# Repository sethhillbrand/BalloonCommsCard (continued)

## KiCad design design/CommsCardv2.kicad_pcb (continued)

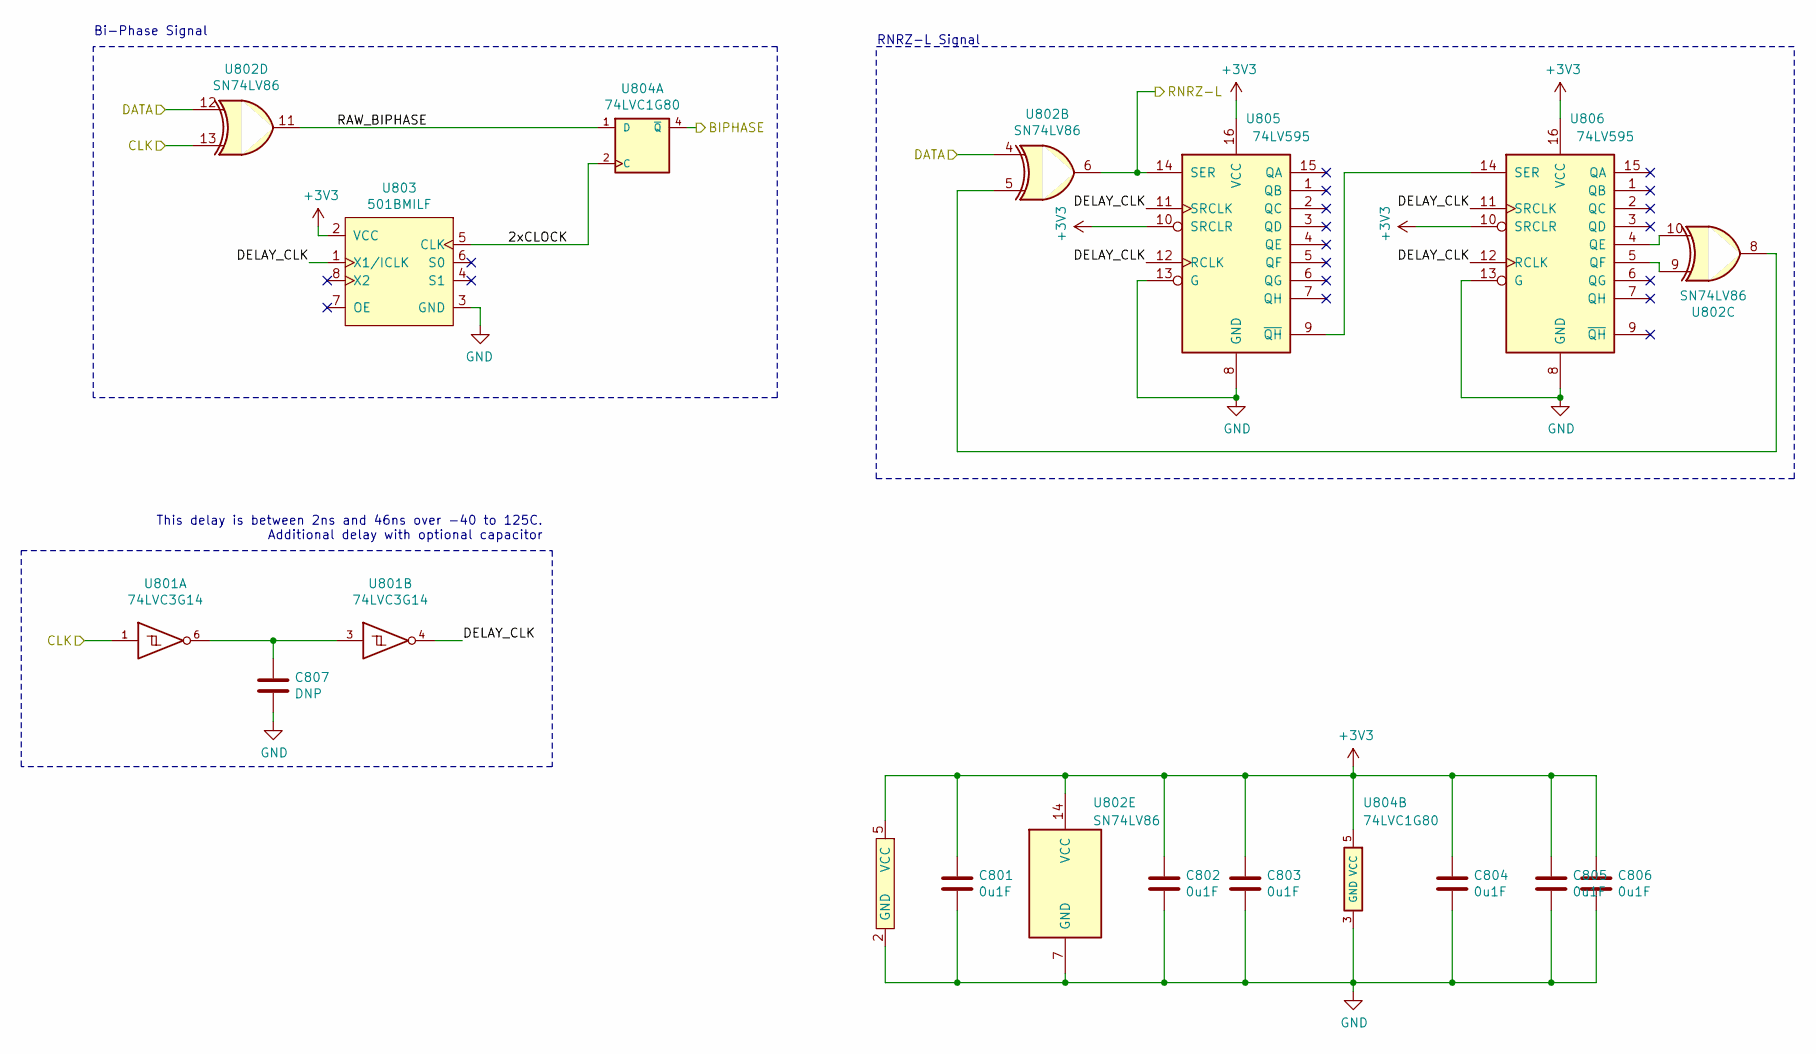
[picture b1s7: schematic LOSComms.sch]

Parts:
C601, C602, C603, C604, C605, C606: 0u1F; C_0603_1608Metric; mpn CL10B104KO8WPNC
C607: DNP; C_0603_1608Metric
U601: 74LVC3G14; SOT-363_SC-70-6; mpn 74LVC14AT14-13
U602: SN74LV86; TSSOP-14_4.4x5mm_P0.65mm; mpn SN74LV86ATPWREP
U603: 501BMILF; SOIC-8_3.9x4.9mm_P1.27mm; mpn 501BMILF
U604: 74LVC1G80; SOT-353_SC-70-5; mpn SN74LVC1G79DCKR
U605, U606: 74LV595; TSSOP-16_4.4x5mm_P0.65mm; mpn SN74LV595APWR

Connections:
/FlightComputer1/LOSComms/2xCLOCK: U603.5 (CLK), U604.2 (C)
/FlightComputer1/LOSComms/BIPHASE: U604.4 (~Q); also elsewhere on the board
/FlightComputer1/LOSComms/CLK: U601.1, U602.2, U602.13; also elsewhere on the board
/FlightComputer1/LOSComms/DATA: U602.1, U602.4, U602.12; also elsewhere on the board
/FlightComputer1/LOSComms/DELAY_CLK: U601.4, U603.1 (X1/ICLK), U605.11 (SRCLK), U605.12 (RCLK), U606.11 (SRCLK), U606.12 (RCLK)
/FlightComputer1/LOSComms/RAW_BIPHASE: U602.3, U602.11, U604.1 (D)
/FlightComputer1/LOSComms/RNRZ-L: U602.6, U605.14 (SER); also elsewhere on the board
GND: C601.2, C602.2, C603.2, C604.2, C605.2, C606.2, C607.2, U601.2 (GND), U602.7 (GND), U603.3 (GND), U604.3 (GND), U605.8 (GND), U605.13 (G), U606.8 (GND), U606.13 (G); also elsewhere on the board
unnamed: C607.1, U601.3, U601.6
unnamed: U602.5, U602.8
unnamed: U602.9, U606.5 (QF)
unnamed: U602.10, U606.4 (QE)
unnamed: U605.9 (~QH), U606.14 (SER)

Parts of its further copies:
C801, C802, C803, C804, C805, C806: 0u1F; C_0603_1608Metric; mpn CL10B104KO8WPNC
C807: DNP; C_0603_1608Metric
U801: 74LVC3G14; SOT-363_SC-70-6; mpn 74LVC14AT14-13
U802: SN74LV86; TSSOP-14_4.4x5mm_P0.65mm; mpn SN74LV86ATPWREP
U803: 501BMILF; SOIC-8_3.9x4.9mm_P1.27mm; mpn 501BMILF
U804: 74LVC1G80; SOT-353_SC-70-5; mpn SN74LVC1G79DCKR
U805, U806: 74LV595; TSSOP-16_4.4x5mm_P0.65mm; mpn SN74LV595APWR

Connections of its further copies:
/FlightComputer2/LOSComms/2xCLOCK: U803.5 (CLK), U804.2 (C)
/FlightComputer2/LOSComms/BIPHASE: U804.4 (~Q); also elsewhere on the board
/FlightComputer2/LOSComms/CLK: U801.1, U802.13; also elsewhere on the board
/FlightComputer2/LOSComms/DATA: U802.4, U802.12; also elsewhere on the board
/FlightComputer2/LOSComms/DELAY_CLK: U801.4, U803.1 (X1/ICLK), U805.11 (SRCLK), U805.12 (RCLK), U806.11 (SRCLK), U806.12 (RCLK)
/FlightComputer2/LOSComms/RAW_BIPHASE: U802.11, U804.1 (D)
/FlightComputer2/LOSComms/RNRZ-L: U802.6, U805.14 (SER); also elsewhere on the board
GND: C801.2, C802.2, C803.2, C804.2, C805.2, C806.2, C807.2, U801.2 (GND), U802.7 (GND), U803.3 (GND), U804.3 (GND), U805.8 (GND), U805.13 (G), U806.8 (GND), U806.13 (G); also elsewhere on the board
unnamed: C807.1, U801.3, U801.6
unnamed: U802.5, U802.8
unnamed: U802.9, U806.5 (QF)
unnamed: U802.10, U806.4 (QE)
unnamed: U805.9 (~QH), U806.14 (SER)

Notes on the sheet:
RNRZ-L Signal
This delay is between 2ns and 46ns over -40 to 125C. Additional delay with optional capacitor
Bi-Phase Signal

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
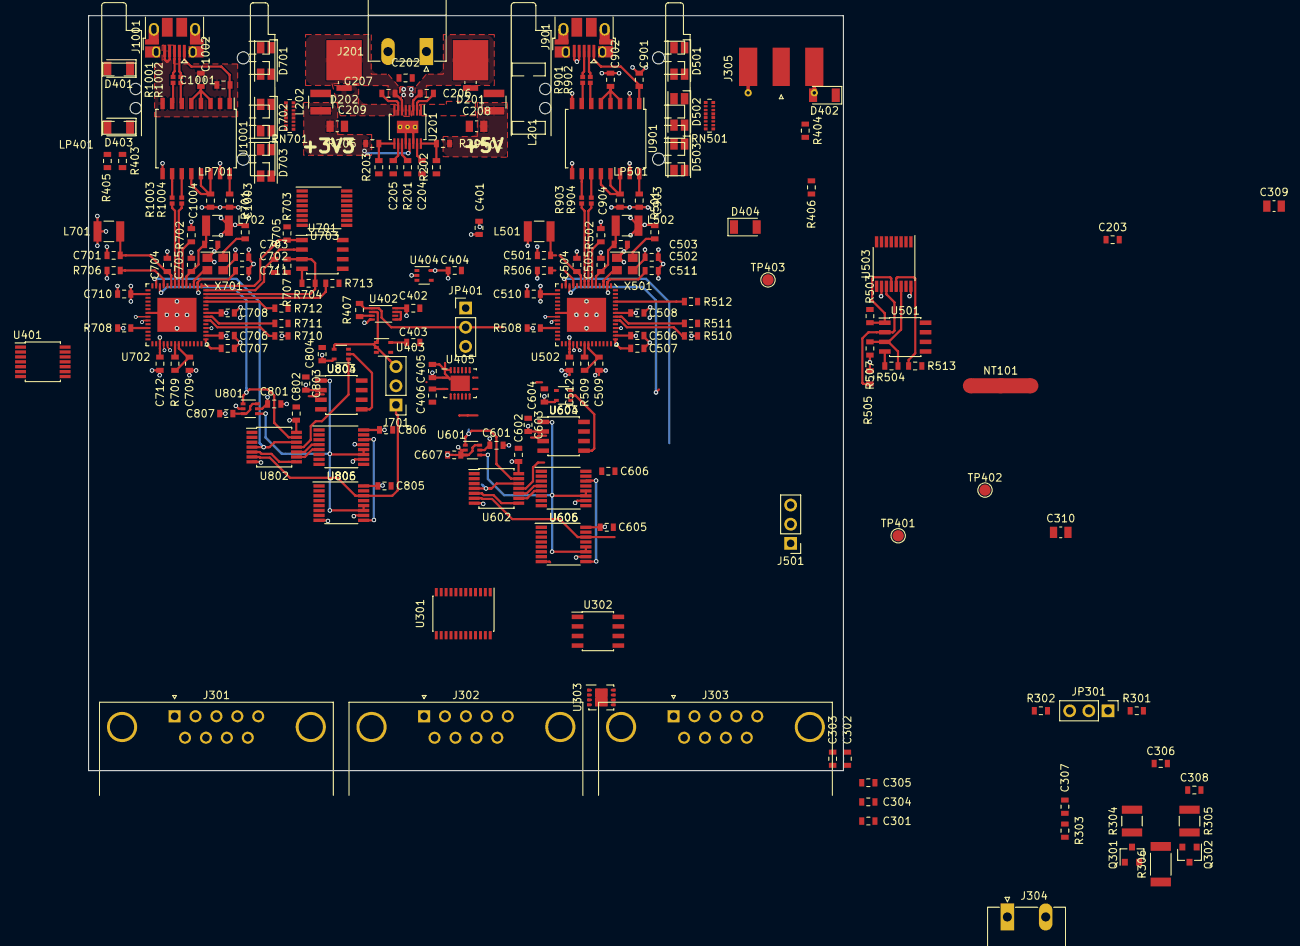
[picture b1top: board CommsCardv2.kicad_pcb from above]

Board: 4 copper layers, 100.0 x 100.0 mm, 194 parts (1 on the bottom side), 182 nets.

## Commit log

2018-02-07 Adding changelog
2018-02-07 Adding rev0 readme
2018-02-07 Adding CommsCard basic layout
2018-02-07 Adding project symbol library table
2018-02-07 Adding Input Schematic
2018-02-07 Adding watchdog
2018-02-08 Adding TI footprint and watchdog stuff
2018-02-08 Updating wd
2018-02-08 Adding power and external connector components
2018-02-08 Adding LT39509 regulator for voltage levels
2018-02-08 adding power input connectors
2018-02-08 Remove annotation
2018-02-09 Connecting LOS inside FC connection
2018-02-09 Adding RS232
2018-02-10 Adding RS-232 Ports
2018-02-10 Renaming RS232 and adding LOS Comms
2018-02-10 Adding Drivers for RS422 and high power LOS
2018-02-10 Adding missing LOS wire
2018-02-11 Finished ERC
2018-02-11 Adding LED Indicator for tx/rx
2018-02-13 Adding more indicators
2018-02-14 Swapping FT4232 for VQFN and finalizing mpns
2018-02-14 Removing erroneous project file
2018-02-15 Fix pin numbering on resistor array
2018-02-15 Initial layout work
2018-02-15 Updating schematic for layout
2018-02-15 Switching PLL inductor
2018-02-15 Correcting PLL wiring
2018-02-15 Updating capacitors for 56pin
2018-02-15 Placing caps
2018-02-16 Renumber and sub clock generator
2018-02-17 Annotating
2018-02-18 Simplify Watchdog
2018-02-18 Label power nets
2018-02-18 Propogate Power nets
2018-02-18 Further Layout work
2018-02-19 Further routing
2018-02-20 Finish Power layout
2018-02-21 Layout USB Interface
2018-02-22 Layout FC1 FT Chip
2018-02-23 Finish FC1 layout
2018-02-28 Duplicating FC1
2018-03-01 Duplicate fills for FC2
2018-03-01 Fixing ERC power flag
2018-03-01 Adding labels to LOS nets
2018-03-01 Add 5V power to USB isolator
2018-03-01 Reversing pins
2018-03-01 Update USB bypass
2018-03-01 Begin layout for high-rate data
2018-03-03 Adjusting LOS
2018-03-10 Layout additional watchdog
2018-03-13 Adding more LOS detail
2018-03-15 Changing to dual-gate inverters for delay line
2018-03-16 Finalizing FC1 --- ish
2018-03-17 Further LOS updates. Compressing space
2018-03-17 Adding LEDs
2018-03-17 Minimizing space in design
2018-03-18 Switching to light pipes for LEDs
2018-03-21 Adding smaller light pipe and compressing power input
2018-03-22 Additional work on power input
